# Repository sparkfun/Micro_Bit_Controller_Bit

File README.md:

SparkFun controller:bit - micro:bit Carrier Board (Qwiic)
========================================

<table class="table table-hover table-striped table-bordered">
  <tr align="center">
   <td></td>
   <td></td>
  </tr>
  <tr align="center">
   <td><i>SparkFun controller:bit - micro:bit Carrier Board (Qwiic)<br /> [ <a href="https://www.sparkfun.com/products/16129">DEV-16129</a> ]</i></td>
   <td><i>SparkFun micro:arcade kit for micro:bit v2.0 <br />[ <a href="https://www.sparkfun.com/products/16403">KIT-16403</a> ]</i></td>
  </tr>
</table>

The SparkFun controller:bit is a fun-filled “carrier” board for the micro:bit that, when combined with the micro:bit, provides you with a fully functional game system. Designed in a similar form factor to the classic Nintendo NES controller, the controller:bit is equipped with a four-direction “D-pad” on the left side of the board and two action buttons on the right side of the board. The two push buttons on the micro:bit in the center function as start and select. The back of the board also includes poke-home connectors if you decide to go retro by connecting connect arcade buttons and switches. Check out the micro:arcade kit if you decide to build your very own arcade cabinet using the micro:bit!

Repository Contents
-------------------

* **/Firmware** - Example code 
* **/Hardware** - Eagle design files (.brd, .sch)
* **/Hardware/Production** - Production panel files (.brd)

Documentation
--------------
* **[Library](https://github.com/sparkfun/pxt-gamer-bit)** - PXT controller:bit firmware
* **[Micro:Arcade Kit Experiment Guide](https://learn.sparkfun.com/tutorials/microarcade-kit-experiment-guide/)** -  Experiment guide using the controller:bit carrier board.
* **[Wireless Remote Control with micro:bit](https://learn.sparkfun.com/tutorials/wireless-remote-control-with-microbit)** - Project guide using the micro:bot and micro:arcade kits. By utilizing the radio blocks, you can wirelessly control the micro:bot using the controller:bit.

Version History
---------------

* [SparkFun controller:bit - micro:bit Carrier Board (Qwiic)](https://www.sparkfun.com/products/16129) - Latest and greatest (has qwiic connector)
* [SparkFun gamer:bit](https://www.sparkfun.com/products/14215) - Initial product (no qwiic connector)

Product Versions
----------------

* [KIT-16403](https://www.sparkfun.com/products/16403) - Kit with the controller:bit
* [DEV-16129](https://www.sparkfun.com/products/16129) - V21, revision and renamed as controller:bit
* [KIT-14218](https://www.sparkfun.com/products/14218) - Kit with the gamer:bit
* [DEV-14215](https://www.sparkfun.com/products/14215) - v10, Initial release as the gamer:bit

License Information
-------------------

This product is _**open source**_! 

Please review the LICENSE.md file for license information. 

If you have any questions or concerns on licensing, please contact technical support on our [SparkFun forums](https://forum.sparkfun.com/viewforum.php?f=152).

Distributed as-is; no warranty is given.

- Your friends at SparkFun.

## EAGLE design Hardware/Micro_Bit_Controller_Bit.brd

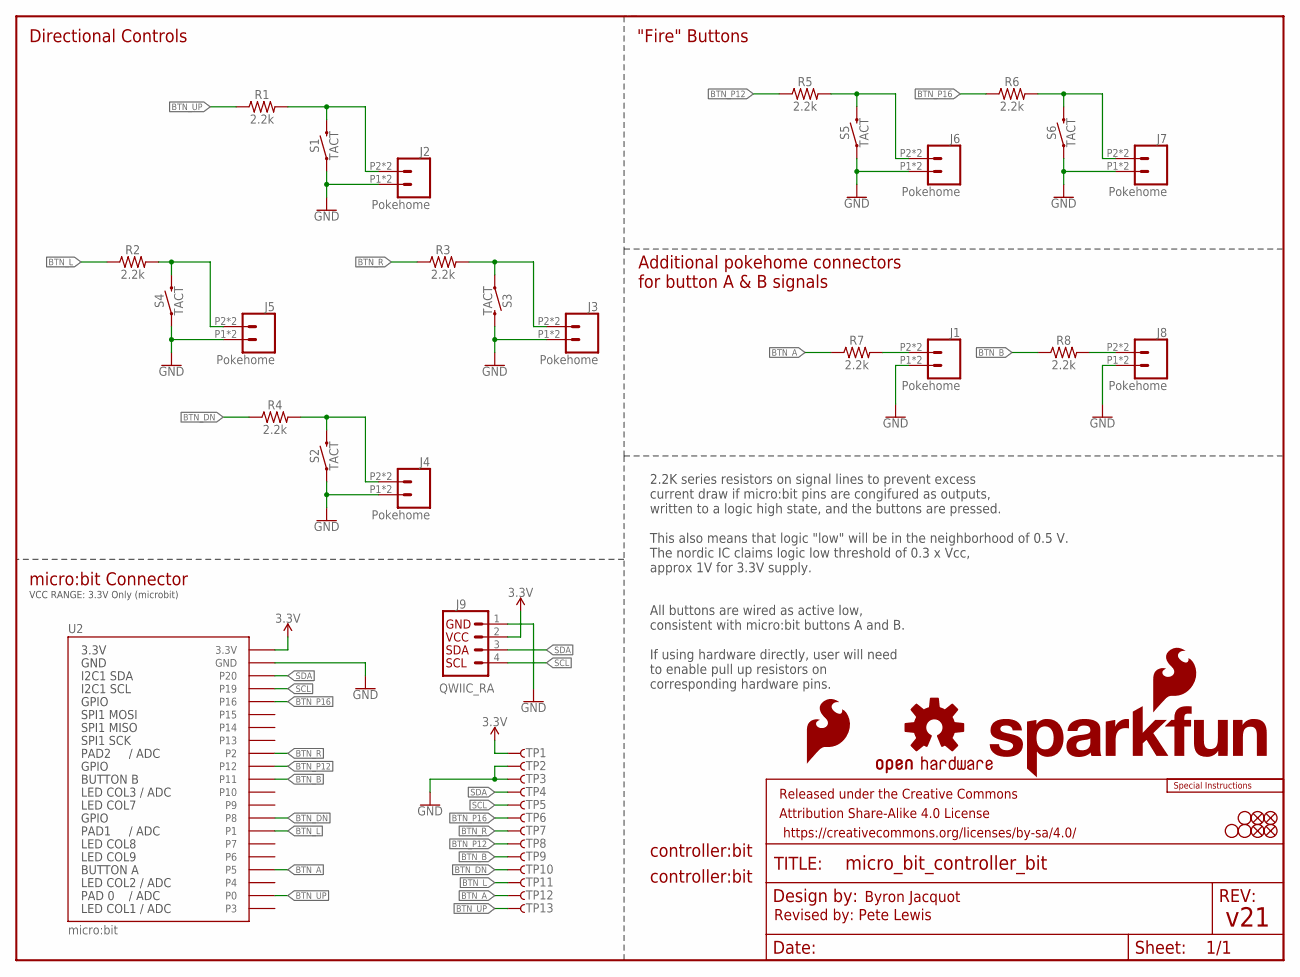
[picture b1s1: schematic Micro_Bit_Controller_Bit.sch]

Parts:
FD1, FD2, FD3, FD4: FIDUCIALUFIDUCIAL; FIDUCIAL-MICRO
FRAME1: FRAME-LETTER; CREATIVE_COMMONS
H1, H2, H3: STAND-OFF
J1, J2, J3, J4, J5, J6, J7, J8: Pokehome; 1X02_POKEHOME
J9: QWIIC_RA; JST04_1MM_RA
LOGO1: SFE_LOGO_FLAME.2_INCH; SFE_LOGO_FLAME_.2
LOGO2: OSHW-LOGOL; OSHW-LOGO-L
LOGO3: SFE_LOGO_NAME_FLAME.3_INCH; SFE_LOGO_NAME_FLAME_.3
R1, R2, R3, R4, R5, R6, R7, R8: 2.2k; 0603
S1, S2, S3, S4, S5, S6: TACT; TACTILE_SWITCH_SMD_12MM
TP1, TP2, TP3, TP4, TP5, TP6, TP7, TP8, TP9, TP10, TP11, TP12, TP13: TEST-POINT3X5; PAD.03X.05
U2: micro:bit; MICRO:BIT-RA_SMD
U$1: SPECIAL_INSTRUCTIONS-ORDERING; ORDERING_INSTRUCTIONS
U$3, U$6: LOGO-CONTROLLER_BIT

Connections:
3.3V: J9.2, TP1.P$1, U2.P$27 (3.3V), U2.P$28 (3.3V), U2.P$29 (3.3V), U2.P$30 (3.3V), U2.P$31 (3.3V), U2.P$32 (3.3V)
BTN_A: R7.1, TP12.P$1, U2.P$7 (P5)
BTN_B: R8.1, TP9.P$1, U2.P$17 (P11)
BTN_DN: R4.1, TP10.P$1, U2.P$14 (P8)
BTN_L: R2.1, TP11.P$1, U2.P$10 (P1), U2.P$11 (P1), U2.P$12 (P1), U2.P$13 (P1)
BTN_P12: R5.1, TP8.P$1, U2.P$18 (P12)
BTN_P16: R6.1, TP6.P$1, U2.P$26 (P16)
BTN_R: R3.1, TP7.P$1, U2.P$19 (P2), U2.P$20 (P2), U2.P$21 (P2), U2.P$22 (P2)
BTN_UP: R1.1, TP13.P$1, U2.P$2 (P0), U2.P$3 (P0), U2.P$4 (P0), U2.P$5 (P0)
GND: J1.P1 (1), J1.P3 (1), J2.P1 (1), J2.P3 (1), J3.P1 (1), J3.P3 (1), J4.P1 (1), J4.P3 (1), J5.P1 (1), J5.P3 (1), J6.P1 (1), J6.P3 (1), J7.P1 (1), J7.P3 (1), J8.P1 (1), J8.P3 (1), J9.1, S1.1, S2.1, S3.3 (2), S4.1, S5.1, S6.1, TP2.P$1, TP3.P$1, U2.P$35 (GND), U2.P$36 (GND), U2.P$37 (GND), U2.P$38 (GND), U2.P$39 (GND), U2.P$40 (GND)
unnamed: J2.P2 (2), J2.P4 (2), R1.2, S1.3 (2)
unnamed: J5.P2 (2), J5.P4 (2), R2.2, S4.3 (2)
unnamed: J4.P2 (2), J4.P4 (2), R4.2, S2.3 (2)
unnamed: J3.P2 (2), J3.P4 (2), R3.2, S3.1
unnamed: J7.P2 (2), J7.P4 (2), R6.2, S6.3 (2)
unnamed: J8.P2 (2), J8.P4 (2), R8.2
unnamed: J1.P2 (2), J1.P4 (2), R7.2
unnamed: J6.P2 (2), J6.P4 (2), R5.2, S5.3 (2)
SCL: J9.4, TP5.P$1, U2.P$33 (P19)
SDA: J9.3, TP4.P$1, U2.P$34 (P20)

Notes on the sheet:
Byron Jacquot
v21
All buttons are wired as active low, consistent with micro:bit buttons A and B. If using hardware directly, user will need to enable pull up resistors on corresponding hardware pins.
2.2K series resistors on signal lines to prevent excess current draw if micro:bit pins are congifured as outputs, written to a logic high state, and the buttons are pressed. This also means that logic "low" will be in the neighborhood of 0.5 V. The nordic IC claims logic low threshold of 0.3 x Vcc,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
Additional pokehome connectors for button A & B signals
Directional Controls
"Fire" Buttons
micro:bit Connector
Revised by: Pete Lewis
VCC RANGE: 3.3V Only (microbit)

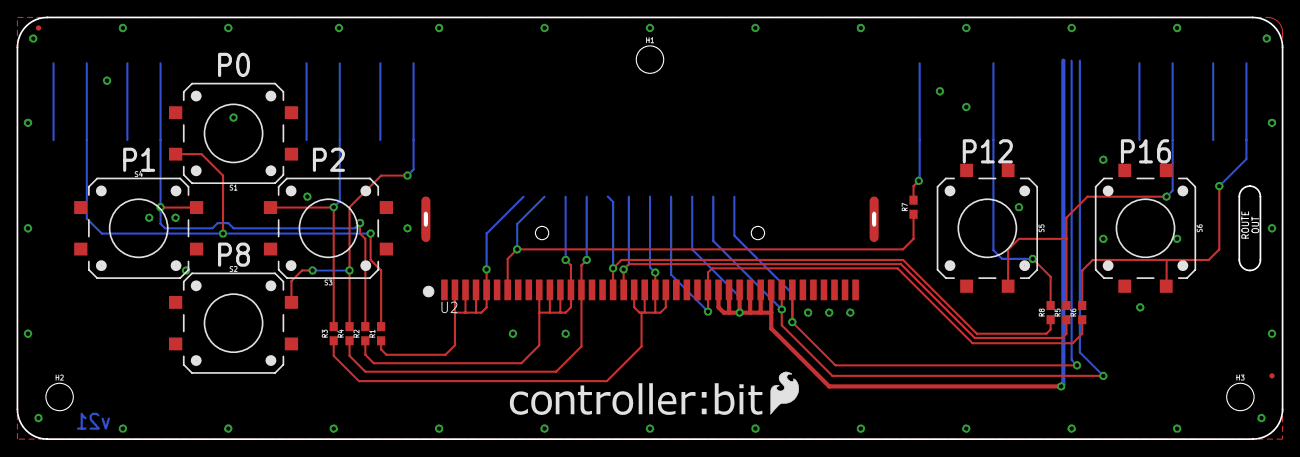
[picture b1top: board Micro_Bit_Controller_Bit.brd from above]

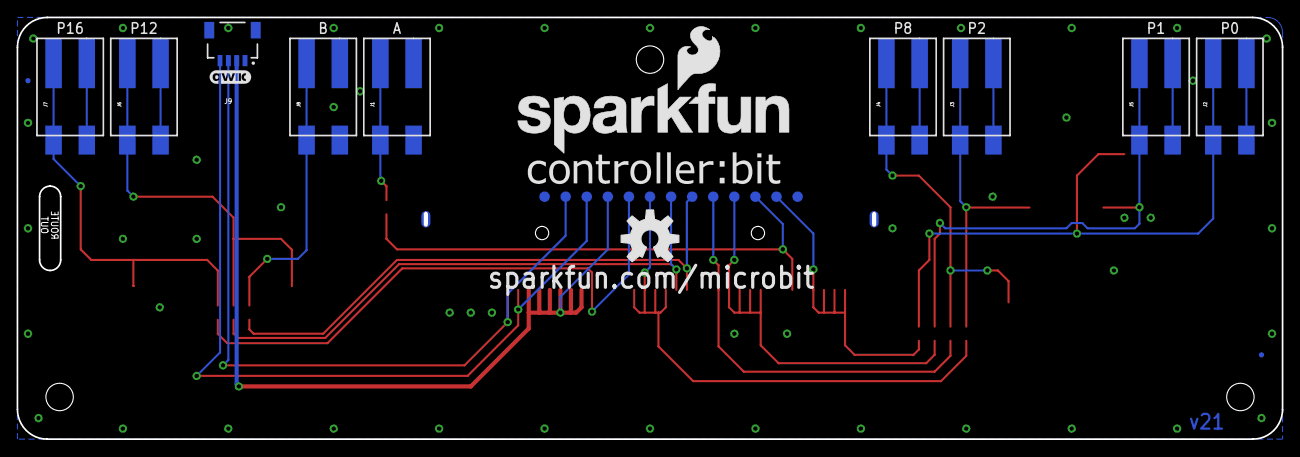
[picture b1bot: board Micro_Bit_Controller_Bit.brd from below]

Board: 2 copper layers, 152.1 x 50.5 mm, 52 parts (28 on the bottom side), 20 nets.

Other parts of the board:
U$2: QWIIC_5MM

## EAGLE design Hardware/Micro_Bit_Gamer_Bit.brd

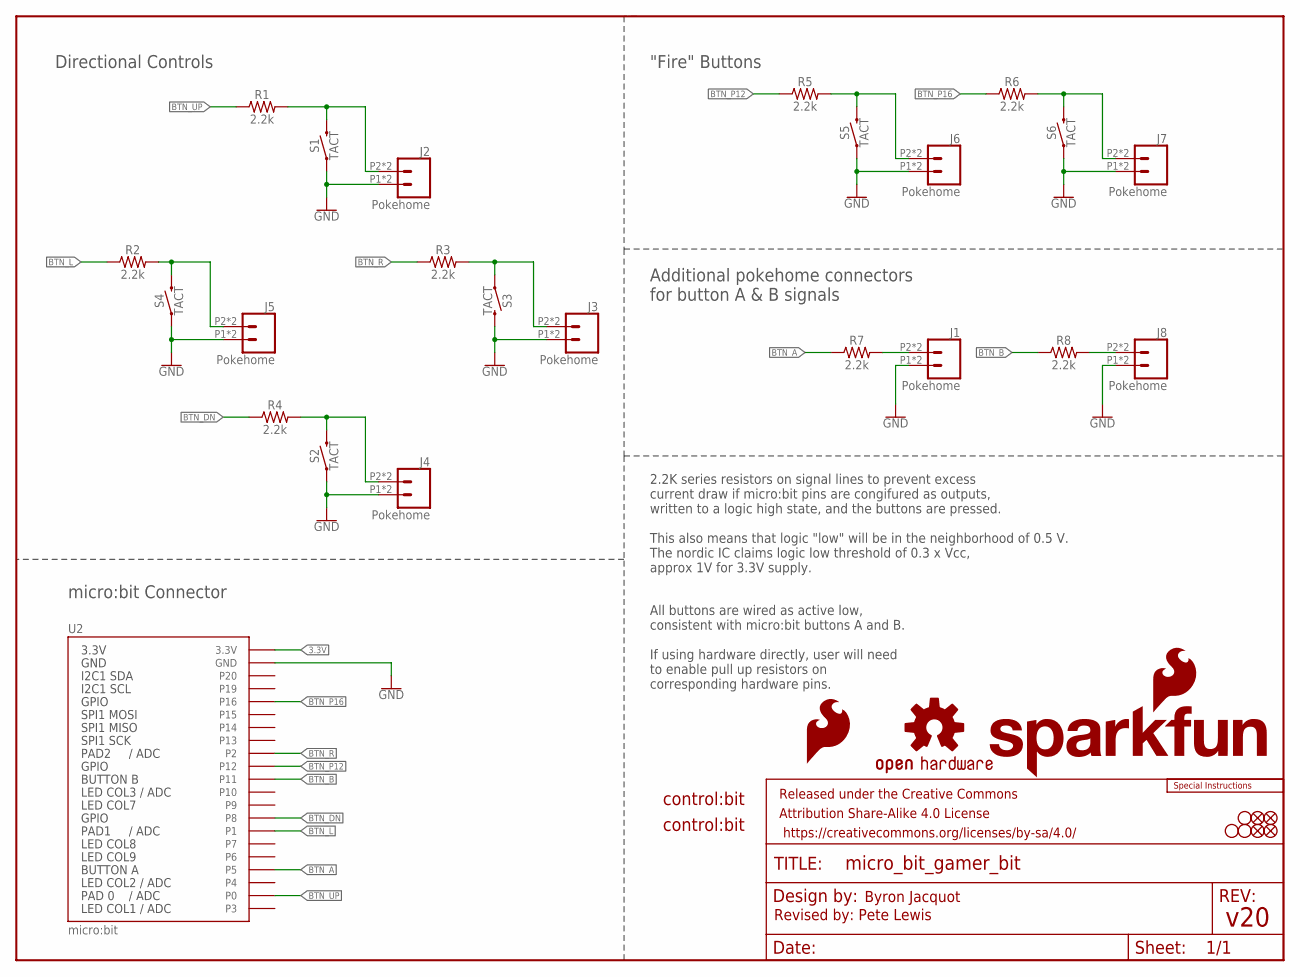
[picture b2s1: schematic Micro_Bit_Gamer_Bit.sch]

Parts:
FD1, FD2, FD3, FD4: FIDUCIALUFIDUCIAL; FIDUCIAL-MICRO
FRAME1: FRAME-LETTER; CREATIVE_COMMONS
H1, H2, H3: STAND-OFF
J1, J2, J3, J4, J5, J6, J7, J8: Pokehome; 1X02_POKEHOME
LOGO1: SFE_LOGO_FLAME.2_INCH; SFE_LOGO_FLAME_.2
LOGO2: OSHW-LOGOL; OSHW-LOGO-L
LOGO3: SFE_LOGO_NAME_FLAME.3_INCH; SFE_LOGO_NAME_FLAME_.3
R1, R2, R3, R4, R5, R6, R7, R8: 2.2k; 0603
S1, S2, S3, S4, S5, S6: TACT; TACTILE_SWITCH_SMD_12MM
U2: micro:bit; MICRO:BIT-RA_SMD
U$1: SPECIAL_INSTRUCTIONS-ORDERING; ORDERING_INSTRUCTIONS
U$4, U$5: LOGO-CONTROLBIT

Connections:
3.3V: U2.P$27 (3.3V), U2.P$28 (3.3V), U2.P$29 (3.3V), U2.P$30 (3.3V), U2.P$31 (3.3V), U2.P$32 (3.3V); also elsewhere on the board
BTN_A: R7.1, U2.P$7 (P5)
BTN_B: R8.1, U2.P$17 (P11)
BTN_DN: R4.1, U2.P$14 (P8)
BTN_L: R2.1, U2.P$10 (P1), U2.P$11 (P1), U2.P$12 (P1), U2.P$13 (P1)
BTN_P12: R5.1, U2.P$18 (P12)
BTN_P16: R6.1, U2.P$26 (P16)
BTN_R: R3.1, U2.P$19 (P2), U2.P$20 (P2), U2.P$21 (P2), U2.P$22 (P2)
BTN_UP: R1.1, U2.P$2 (P0), U2.P$3 (P0), U2.P$4 (P0), U2.P$5 (P0)
GND: J1.P1 (1), J1.P3 (1), J2.P1 (1), J2.P3 (1), J3.P1 (1), J3.P3 (1), J4.P1 (1), J4.P3 (1), J5.P1 (1), J5.P3 (1), J6.P1 (1), J6.P3 (1), J7.P1 (1), J7.P3 (1), J8.P1 (1), J8.P3 (1), S1.1, S2.1, S3.3 (2), S4.1, S5.1, S6.1, U2.P$35 (GND), U2.P$36 (GND), U2.P$37 (GND), U2.P$38 (GND), U2.P$39 (GND), U2.P$40 (GND); also elsewhere on the board
unnamed: J2.P2 (2), J2.P4 (2), R1.2, S1.3 (2)
unnamed: J5.P2 (2), J5.P4 (2), R2.2, S4.3 (2)
unnamed: J4.P2 (2), J4.P4 (2), R4.2, S2.3 (2)
unnamed: J3.P2 (2), J3.P4 (2), R3.2, S3.1
unnamed: J7.P2 (2), J7.P4 (2), R6.2, S6.3 (2)
unnamed: J8.P2 (2), J8.P4 (2), R8.2
unnamed: J1.P2 (2), J1.P4 (2), R7.2
unnamed: J6.P2 (2), J6.P4 (2), R5.2, S5.3 (2)
SCL: U2.P$33 (P19); also elsewhere on the board
SDA: U2.P$34 (P20); also elsewhere on the board

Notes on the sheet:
Byron Jacquot
v20
All buttons are wired as active low, consistent with micro:bit buttons A and B. If using hardware directly, user will need to enable pull up resistors on corresponding hardware pins.
2.2K series resistors on signal lines to prevent excess current draw if micro:bit pins are congifured as outputs, written to a logic high state, and the buttons are pressed. This also means that logic "low" will be in the neighborhood of 0.5 V. The nordic IC claims logic low threshold of 0.3 x Vcc,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
Additional pokehome connectors for button A & B signals
Directional Controls
"Fire" Buttons
micro:bit Connector
Revised by: Pete Lewis

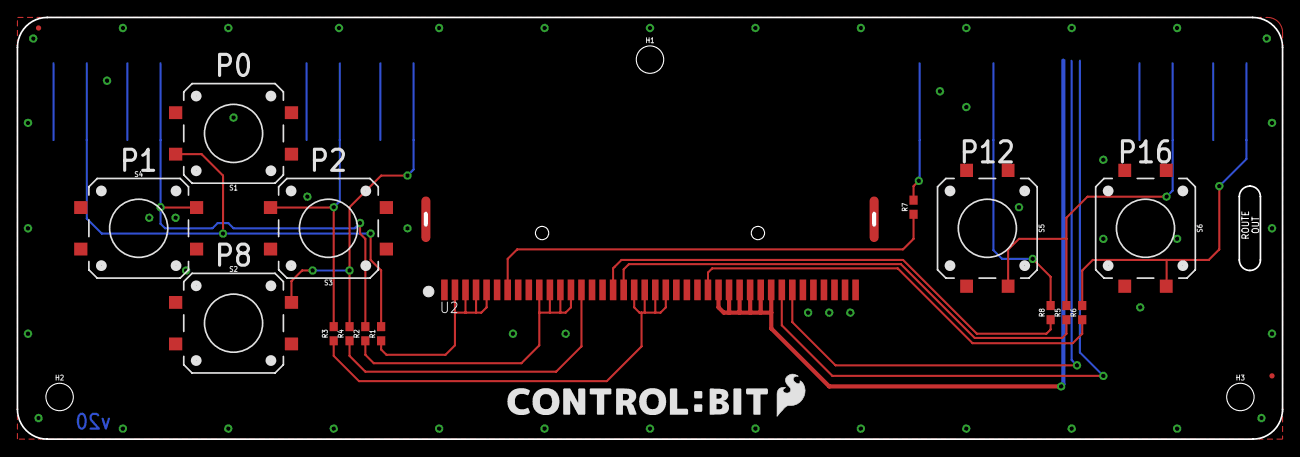
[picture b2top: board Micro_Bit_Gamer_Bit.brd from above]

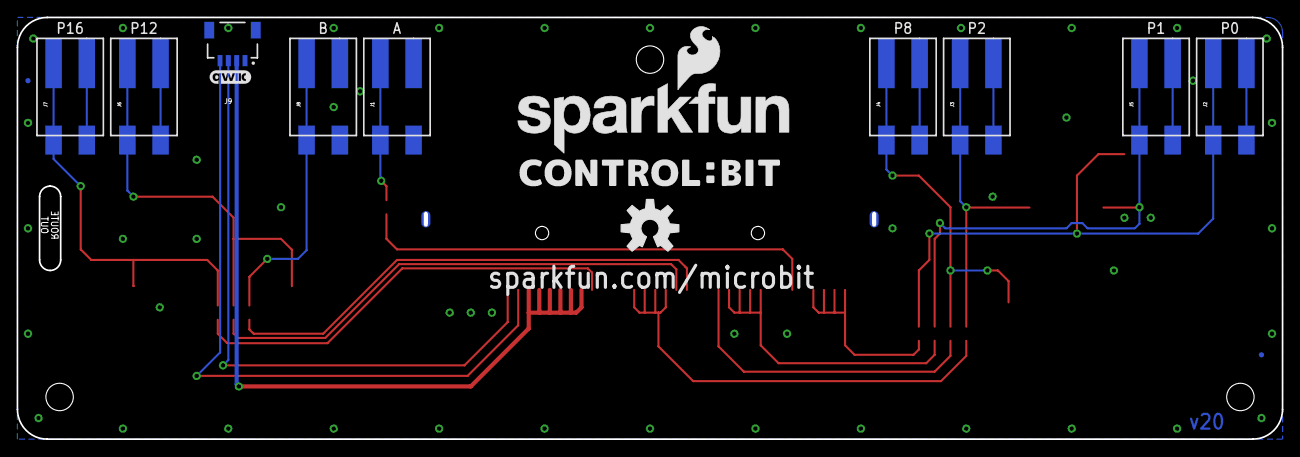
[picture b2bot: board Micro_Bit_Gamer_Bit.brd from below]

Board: 2 copper layers, 152.1 x 50.5 mm, 39 parts (15 on the bottom side), 20 nets.

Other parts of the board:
J9: QWIIC_RA; JST04_1MM_RA
U$2: QWIIC_5MM

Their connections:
3.3V: J9.2; also elsewhere on the board
GND: J9.1; also elsewhere on the board
SCL: J9.4; also elsewhere on the board
SDA: J9.3; also elsewhere on the board

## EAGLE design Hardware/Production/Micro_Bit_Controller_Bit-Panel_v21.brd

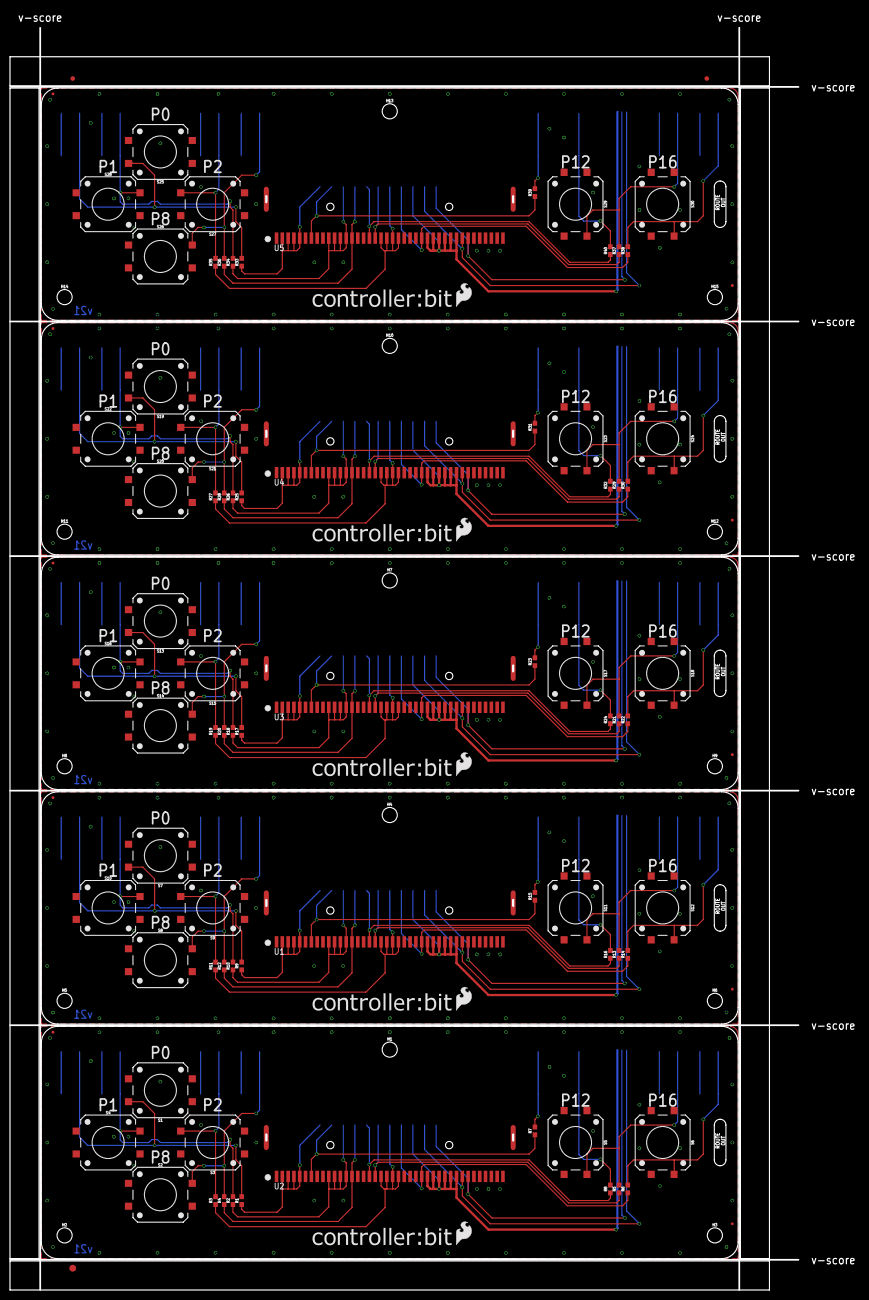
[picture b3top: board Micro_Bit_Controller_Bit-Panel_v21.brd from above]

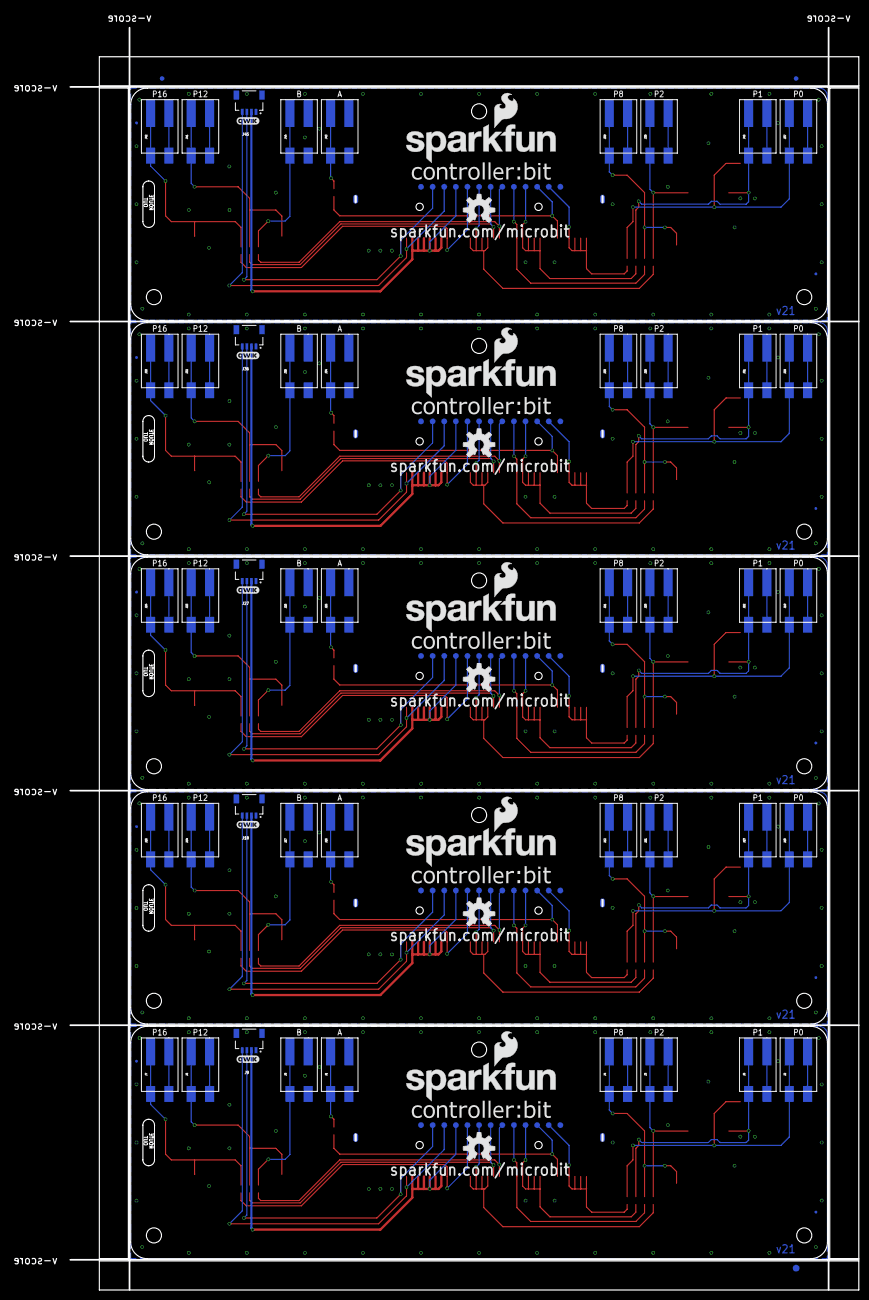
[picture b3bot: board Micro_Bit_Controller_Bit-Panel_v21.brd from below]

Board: 2 copper layers, 185.5 x 279.8 mm, 256 parts (143 on the bottom side), 100 nets.

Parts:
E$1, E$2, E$3, E$4: FIDUCIAL-1X2
E$5, E$6: FIDUCIAL-1.5X3
FD1, FD2, FD3, FD4, FD5, FD6, FD7, FD8, FD9, FD10, FD11, FD12, FD13, FD14, FD15, FD16, FD17, FD18, FD19, FD20: FIDUCIALUFIDUCIAL; FIDUCIAL-MICRO
H1, H2, H3, H4, H5, H6, H7, H8, H9, H10, H11, H12, H13, H14, H15: STAND-OFF
J1, J2, J3, J4, J5, J6, J7, J8, J10, J11, J12, J13, J14, J15, J16, J17, J19, J20, J21, J22, J23, J24, J25, J26, J28, J29, J30, J31, J32, J33, J34, J35, J37, J38, J39, J40, J41, J42, J43, J44: Pokehome; 1X02_POKEHOME
J9, J18, J27, J36, J45: QWIIC_RA; JST04_1MM_RA
LOGO1, LOGO4, LOGO7, LOGO10, LOGO13: SFE_LOGO_FLAME.2_INCH; SFE_LOGO_FLAME_.2
LOGO2, LOGO5, LOGO8, LOGO11, LOGO14: OSHW-LOGOL; OSHW-LOGO-L
LOGO3, LOGO6, LOGO9, LOGO12, LOGO15: SFE_LOGO_NAME_FLAME.3_INCH; SFE_LOGO_NAME_FLAME_.3
R1, R2, R3, R4, R5, R6, R7, R8, R9, R10, R11, R12, R13, R14, R15, R16, R17, R18, R19, R20, R21, R22, R23, R24, R25, R26, R27, R28, R29, R30, R31, R32, R33, R34, R35, R36, R37, R38, R39, R40: 2.2k; 0603
S1, S2, S3, S4, S5, S6, S7, S8, S9, S10, S11, S12, S13, S14, S15, S16, S17, S18, S19, S20, S21, S22, S23, S24, S25, S26, S27, S28, S29, S30: TACT; TACTILE_SWITCH_SMD_12MM
TP1, TP2, TP3, TP4, TP5, TP6, TP7, TP8, TP9, TP10, TP11, TP12, TP13, TP14, TP15, TP16, TP17, TP18, TP19, TP20, TP21, TP22, TP23, TP24, TP25, TP26, TP27, TP28, TP29, TP30, TP31, TP32, TP33, TP34, TP35, TP36, TP37, TP38, TP39, TP40, TP41, TP42, TP43, TP44, TP45, TP46, TP47, TP48, TP49, TP50, TP51, TP52, TP53, TP54, TP55, TP56, TP57, TP58, TP59, TP60, TP61, TP62, TP63, TP64, TP65: TEST-POINT3X5; PAD.03X.05
U1, U2, U3, U4, U5: micro:bit; MICRO:BIT-RA_SMD
U$1, U$2, U$7, U$10, U$13: QWIIC_5MM
U$3, U$4, U$5, U$6, U$8, U$9, U$11, U$12, U$14, U$15: LOGO-CONTROLLER_BIT

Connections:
3.3V: J9.2, TP1.P$1, U2.P$27, U2.P$28, U2.P$29, U2.P$30, U2.P$31, U2.P$32
3.3V1: J18.2, TP14.P$1, U1.P$27, U1.P$28, U1.P$29, U1.P$30, U1.P$31, U1.P$32
3.3V2: J27.2, TP27.P$1, U3.P$27, U3.P$28, U3.P$29, U3.P$30, U3.P$31, U3.P$32
3.3V3: J36.2, TP40.P$1, U4.P$27, U4.P$28, U4.P$29, U4.P$30, U4.P$31, U4.P$32
3.3V4: J45.2, TP53.P$1, U5.P$27, U5.P$28, U5.P$29, U5.P$30, U5.P$31, U5.P$32
BTN_A: R7.1, TP12.P$1, U2.P$7
BTN_A1: R15.1, TP25.P$1, U1.P$7
BTN_A2: R23.1, TP38.P$1, U3.P$7
BTN_A3: R31.1, TP51.P$1, U4.P$7
BTN_A4: R39.1, TP64.P$1, U5.P$7
BTN_B: R8.1, TP9.P$1, U2.P$17
BTN_B1: R16.1, TP22.P$1, U1.P$17
BTN_B2: R24.1, TP35.P$1, U3.P$17
BTN_B3: R32.1, TP48.P$1, U4.P$17
BTN_B4: R40.1, TP61.P$1, U5.P$17
BTN_DN: R4.1, TP10.P$1, U2.P$14
BTN_DN1: R12.1, TP23.P$1, U1.P$14
BTN_DN2: R20.1, TP36.P$1, U3.P$14
BTN_DN3: R28.1, TP49.P$1, U4.P$14
BTN_DN4: R36.1, TP62.P$1, U5.P$14
BTN_L: R2.1, TP11.P$1, U2.P$10, U2.P$11, U2.P$12, U2.P$13
BTN_L1: R10.1, TP24.P$1, U1.P$10, U1.P$11, U1.P$12, U1.P$13
BTN_L2: R18.1, TP37.P$1, U3.P$10, U3.P$11, U3.P$12, U3.P$13
BTN_L3: R26.1, TP50.P$1, U4.P$10, U4.P$11, U4.P$12, U4.P$13
BTN_L4: R34.1, TP63.P$1, U5.P$10, U5.P$11, U5.P$12, U5.P$13
BTN_P1: R14.1, TP19.P$1, U1.P$26
BTN_P2: R13.1, TP21.P$1, U1.P$18
BTN_P3: R22.1, TP32.P$1, U3.P$26
BTN_P4: R21.1, TP34.P$1, U3.P$18
BTN_P5: R30.1, TP45.P$1, U4.P$26
BTN_P6: R29.1, TP47.P$1, U4.P$18
BTN_P7: R38.1, TP58.P$1, U5.P$26
BTN_P8: R37.1, TP60.P$1, U5.P$18
BTN_P12: R5.1, TP8.P$1, U2.P$18
BTN_P16: R6.1, TP6.P$1, U2.P$26
BTN_R: R3.1, TP7.P$1, U2.P$19, U2.P$20, U2.P$21, U2.P$22
BTN_R1: R11.1, TP20.P$1, U1.P$19, U1.P$20, U1.P$21, U1.P$22
BTN_R2: R19.1, TP33.P$1, U3.P$19, U3.P$20, U3.P$21, U3.P$22
BTN_R3: R27.1, TP46.P$1, U4.P$19, U4.P$20, U4.P$21, U4.P$22
BTN_R4: R35.1, TP59.P$1, U5.P$19, U5.P$20, U5.P$21, U5.P$22
BTN_UP: R1.1, TP13.P$1, U2.P$2, U2.P$3, U2.P$4, U2.P$5
BTN_UP1: R9.1, TP26.P$1, U1.P$2, U1.P$3, U1.P$4, U1.P$5
BTN_UP2: R17.1, TP39.P$1, U3.P$2, U3.P$3, U3.P$4, U3.P$5
BTN_UP3: R25.1, TP52.P$1, U4.P$2, U4.P$3, U4.P$4, U4.P$5
BTN_UP4: R33.1, TP65.P$1, U5.P$2, U5.P$3, U5.P$4, U5.P$5
GND: J1.P1, J1.P3, J2.P1, J2.P3, J3.P1, J3.P3, J4.P1, J4.P3, J5.P1, J5.P3, J6.P1, J6.P3, J7.P1, J7.P3, J8.P1, J8.P3, J9.1, S1.1, S2.1, S3.3, S4.1, S5.1, S6.1, TP2.P$1, TP3.P$1, U2.P$35, U2.P$36, U2.P$37, U2.P$38, U2.P$39, U2.P$40
GND1: J10.P1, J10.P3, J11.P1, J11.P3, J12.P1, J12.P3, J13.P1, J13.P3, J14.P1, J14.P3, J15.P1, J15.P3, J16.P1, J16.P3, J17.P1, J17.P3, J18.1, S7.1, S8.1, S9.3, S10.1, S11.1, S12.1, TP15.P$1, TP16.P$1, U1.P$35, U1.P$36, U1.P$37, U1.P$38, U1.P$39, U1.P$40
GND2: J19.P1, J19.P3, J20.P1, J20.P3, J21.P1, J21.P3, J22.P1, J22.P3, J23.P1, J23.P3, J24.P1, J24.P3, J25.P1, J25.P3, J26.P1, J26.P3, J27.1, S13.1, S14.1, S15.3, S16.1, S17.1, S18.1, TP28.P$1, TP29.P$1, U3.P$35, U3.P$36, U3.P$37, U3.P$38, U3.P$39, U3.P$40
GND3: J28.P1, J28.P3, J29.P1, J29.P3, J30.P1, J30.P3, J31.P1, J31.P3, J32.P1, J32.P3, J33.P1, J33.P3, J34.P1, J34.P3, J35.P1, J35.P3, J36.1, S19.1, S20.1, S21.3, S22.1, S23.1, S24.1, TP41.P$1, TP42.P$1, U4.P$35, U4.P$36, U4.P$37, U4.P$38, U4.P$39, U4.P$40
GND4: J37.P1, J37.P3, J38.P1, J38.P3, J39.P1, J39.P3, J40.P1, J40.P3, J41.P1, J41.P3, J42.P1, J42.P3, J43.P1, J43.P3, J44.P1, J44.P3, J45.1, S25.1, S26.1, S27.3, S28.1, S29.1, S30.1, TP54.P$1, TP55.P$1, U5.P$35, U5.P$36, U5.P$37, U5.P$38, U5.P$39, U5.P$40
unnamed: J2.P2, J2.P4, R1.2, S1.3
unnamed: J5.P2, J5.P4, R2.2, S4.3
unnamed: J4.P2, J4.P4, R4.2, S2.3
unnamed: J3.P2, J3.P4, R3.2, S3.1
unnamed: J7.P2, J7.P4, R6.2, S6.3
unnamed: J8.P2, J8.P4, R8.2
unnamed: J1.P2, J1.P4, R7.2
unnamed: J10.P2, J10.P4, R9.2, S7.3
unnamed: J13.P2, J13.P4, R10.2, S10.3
unnamed: J12.P2, J12.P4, R12.2, S8.3
unnamed: J11.P2, J11.P4, R11.2, S9.1
unnamed: J14.P2, J14.P4, R13.2, S11.3
unnamed: J15.P2, J15.P4, R14.2, S12.3
unnamed: J16.P2, J16.P4, R15.2
unnamed: J17.P2, J17.P4, R16.2
unnamed: J19.P2, J19.P4, R17.2, S13.3
unnamed: J22.P2, J22.P4, R18.2, S16.3
unnamed: J21.P2, J21.P4, R20.2, S14.3
unnamed: J20.P2, J20.P4, R19.2, S15.1
unnamed: J23.P2, J23.P4, R21.2, S17.3
unnamed: J24.P2, J24.P4, R22.2, S18.3
unnamed: J25.P2, J25.P4, R23.2
unnamed: J26.P2, J26.P4, R24.2
unnamed: J28.P2, J28.P4, R25.2, S19.3
unnamed: J31.P2, J31.P4, R26.2, S22.3
unnamed: J30.P2, J30.P4, R28.2, S20.3
unnamed: J29.P2, J29.P4, R27.2, S21.1
unnamed: J32.P2, J32.P4, R29.2, S23.3
unnamed: J33.P2, J33.P4, R30.2, S24.3
unnamed: J34.P2, J34.P4, R31.2
unnamed: J35.P2, J35.P4, R32.2
unnamed: J37.P2, J37.P4, R33.2, S25.3
unnamed: J40.P2, J40.P4, R34.2, S28.3
unnamed: J39.P2, J39.P4, R36.2, S26.3
unnamed: J38.P2, J38.P4, R35.2, S27.1
unnamed: J41.P2, J41.P4, R37.2, S29.3
unnamed: J42.P2, J42.P4, R38.2, S30.3
unnamed: J43.P2, J43.P4, R39.2
unnamed: J44.P2, J44.P4, R40.2
unnamed: J6.P2, J6.P4, R5.2, S5.3
SCL: J9.4, TP5.P$1, U2.P$33
SCL1: J18.4, TP18.P$1, U1.P$33
SCL2: J27.4, TP31.P$1, U3.P$33
SCL3: J36.4, TP44.P$1, U4.P$33
SCL4: J45.4, TP57.P$1, U5.P$33
SDA: J9.3, TP4.P$1, U2.P$34
SDA1: J18.3, TP17.P$1, U1.P$34
SDA2: J27.3, TP30.P$1, U3.P$34
SDA3: J36.3, TP43.P$1, U4.P$34
SDA4: J45.3, TP56.P$1, U5.P$34

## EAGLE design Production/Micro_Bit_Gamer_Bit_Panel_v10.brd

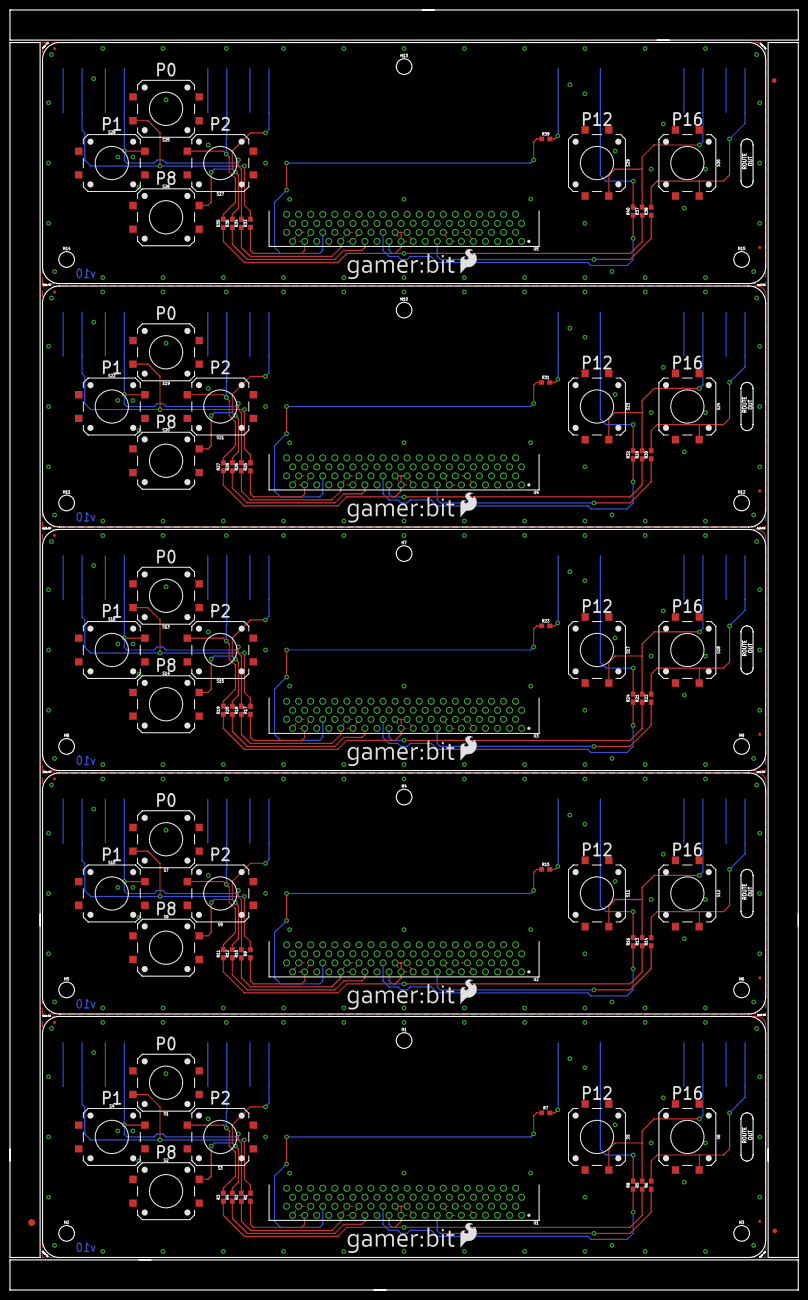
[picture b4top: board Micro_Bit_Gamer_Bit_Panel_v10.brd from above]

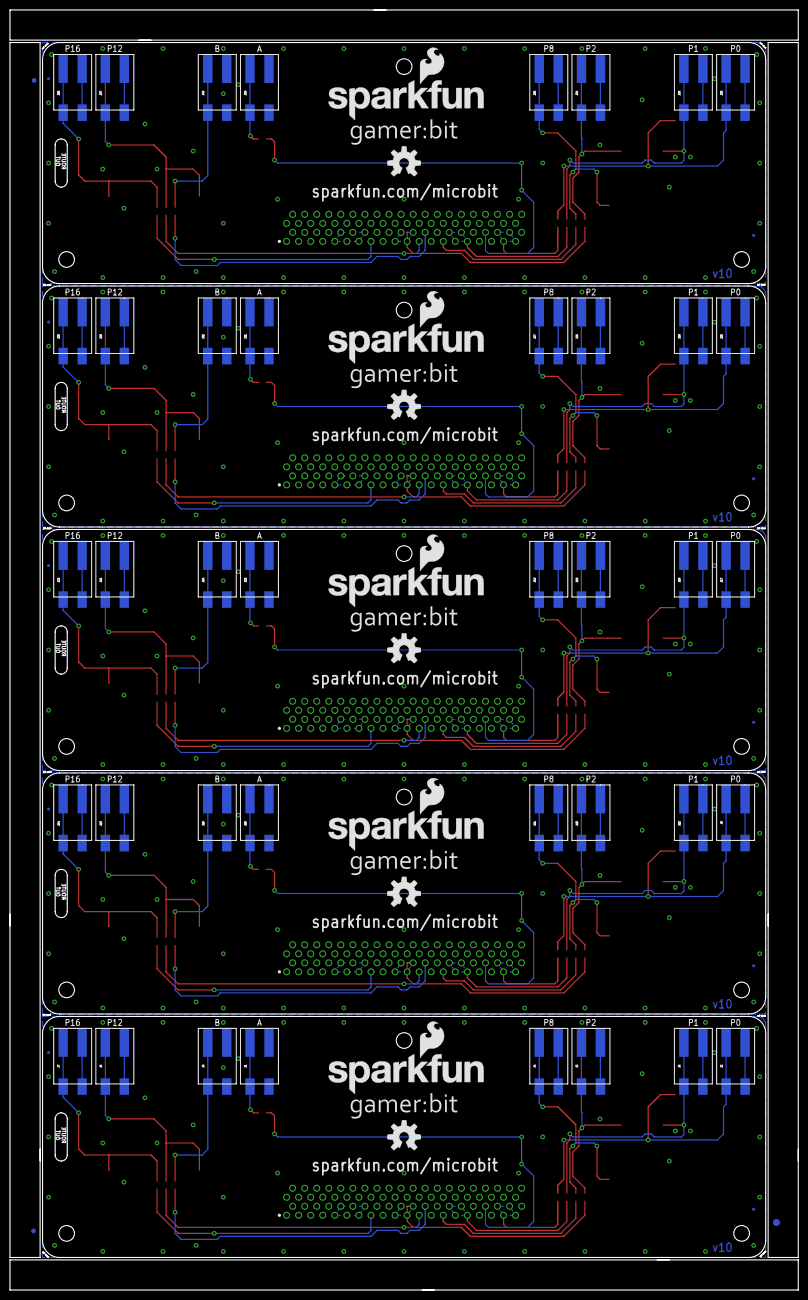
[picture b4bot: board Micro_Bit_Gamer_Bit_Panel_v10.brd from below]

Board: 2 copper layers, 166.1 x 269.7 mm, 181 parts (68 on the bottom side), 90 nets.

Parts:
E$1, E$2: FIDUCIAL-1.5X3
E$3, E$4, E$5, E$7: FIDUCIAL-1X2
FD1, FD2, FD3, FD4, FD5, FD6, FD7, FD8, FD9, FD10, FD11, FD12, FD13, FD14, FD15, FD16, FD17, FD18, FD19, FD20: FIDUCIALUFIDUCIAL; FIDUCIAL-MICRO
H1, H2, H3, H4, H5, H6, H7, H8, H9, H10, H11, H12, H13, H14, H15: STAND-OFF
J1, J2, J3, J4, J5, J6, J7, J8, J9, J10, J11, J12, J13, J14, J15, J16, J17, J18, J19, J20, J21, J22, J23, J24, J25, J26, J27, J28, J29, J30, J31, J32, J33, J34, J35, J36, J37, J38, J39, J40: Pokehome; 1X02_POKEHOME
LOGO1, LOGO4, LOGO7, LOGO10, LOGO13: SFE_LOGO_FLAME.2_INCH; SFE_LOGO_FLAME_.2
LOGO2, LOGO5, LOGO8, LOGO11, LOGO14: OSHW-LOGOL; OSHW-LOGO-L
LOGO3, LOGO6, LOGO9, LOGO12, LOGO15: SFE_LOGO_NAME_FLAME.3_INCH; SFE_LOGO_NAME_FLAME_.3
R1, R2, R3, R4, R5, R6, R7, R8, R9, R10, R11, R12, R13, R14, R15, R16, R17, R18, R19, R20, R21, R22, R23, R24, R25, R26, R27, R28, R29, R30, R31, R32, R33, R34, R35, R36, R37, R38, R39, R40: 2.2k; 0603
S1, S2, S3, S4, S5, S6, S7, S8, S9, S10, S11, S12, S13, S14, S15, S16, S17, S18, S19, S20, S21, S22, S23, S24, S25, S26, S27, S28, S29, S30: TACT; TACTILE_SWITCH_SMD_12MM
U1, U2, U3, U4, U5: micro:bit; MICRO:BIT_RA_PTH
U$1, U$2, U$3, U$4, U$5, U$6, U$7, U$8, U$9, U$10: LOGO-GAMERBIT

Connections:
3.3V: U1.A9, U1.A10, U1.A11, U1.A12, U1.A13, U1.A14
3.3V1: U2.A9, U2.A10, U2.A11, U2.A12, U2.A13, U2.A14
3.3V2: U3.A9, U3.A10, U3.A11, U3.A12, U3.A13, U3.A14
3.3V3: U4.A9, U4.A10, U4.A11, U4.A12, U4.A13, U4.A14
3.3V4: U5.A9, U5.A10, U5.A11, U5.A12, U5.A13, U5.A14
BTN_A: R7.1, U1.A34
BTN_A1: R15.1, U2.A34
BTN_A2: R23.1, U3.A34
BTN_A3: R31.1, U4.A34
BTN_A4: R39.1, U5.A34
BTN_B: R8.1, U1.A24
BTN_B1: R16.1, U2.A24
BTN_B2: R24.1, U3.A24
BTN_B3: R32.1, U4.A24
BTN_B4: R40.1, U5.A24
BTN_DN: R4.1, U1.A27
BTN_DN1: R12.1, U2.A27
BTN_DN2: R20.1, U3.A27
BTN_DN3: R28.1, U4.A27
BTN_DN4: R36.1, U5.A27
BTN_L: R2.1, U1.A28, U1.A29, U1.A30, U1.A31
BTN_L1: R10.1, U2.A28, U2.A29, U2.A30, U2.A31
BTN_L2: R18.1, U3.A28, U3.A29, U3.A30, U3.A31
BTN_L3: R26.1, U4.A28, U4.A29, U4.A30, U4.A31
BTN_L4: R34.1, U5.A28, U5.A29, U5.A30, U5.A31
BTN_P1: R14.1, U2.A15
BTN_P2: R13.1, U2.A23
BTN_P3: R22.1, U3.A15
BTN_P4: R21.1, U3.A23
BTN_P5: R30.1, U4.A15
BTN_P6: R29.1, U4.A23
BTN_P7: R38.1, U5.A15
BTN_P8: R37.1, U5.A23
BTN_P12: R5.1, U1.A23
BTN_P16: R6.1, U1.A15
BTN_R: R3.1, U1.A19, U1.A20, U1.A21, U1.A22
BTN_R1: R11.1, U2.A19, U2.A20, U2.A21, U2.A22
BTN_R2: R19.1, U3.A19, U3.A20, U3.A21, U3.A22
BTN_R3: R27.1, U4.A19, U4.A20, U4.A21, U4.A22
BTN_R4: R35.1, U5.A19, U5.A20, U5.A21, U5.A22
BTN_UP: R1.1, U1.A36, U1.A37, U1.A38, U1.A39
BTN_UP1: R9.1, U2.A36, U2.A37, U2.A38, U2.A39
BTN_UP2: R17.1, U3.A36, U3.A37, U3.A38, U3.A39
BTN_UP3: R25.1, U4.A36, U4.A37, U4.A38, U4.A39
BTN_UP4: R33.1, U5.A36, U5.A37, U5.A38, U5.A39
GND: J1.P1, J1.P3, J2.P1, J2.P3, J3.P1, J3.P3, J4.P1, J4.P3, J5.P1, J5.P3, J6.P1, J6.P3, J7.P1, J7.P3, J8.P1, J8.P3, S1.1, S2.1, S3.3, S4.1, S5.1, S6.1, U1.A1, U1.A2, U1.A3, U1.A4, U1.A5, U1.A6
GND1: J9.P1, J9.P3, J10.P1, J10.P3, J11.P1, J11.P3, J12.P1, J12.P3, J13.P1, J13.P3, J14.P1, J14.P3, J15.P1, J15.P3, J16.P1, J16.P3, S7.1, S8.1, S9.3, S10.1, S11.1, S12.1, U2.A1, U2.A2, U2.A3, U2.A4, U2.A5, U2.A6
GND2: J17.P1, J17.P3, J18.P1, J18.P3, J19.P1, J19.P3, J20.P1, J20.P3, J21.P1, J21.P3, J22.P1, J22.P3, J23.P1, J23.P3, J24.P1, J24.P3, S13.1, S14.1, S15.3, S16.1, S17.1, S18.1, U3.A1, U3.A2, U3.A3, U3.A4, U3.A5, U3.A6
GND3: J25.P1, J25.P3, J26.P1, J26.P3, J27.P1, J27.P3, J28.P1, J28.P3, J29.P1, J29.P3, J30.P1, J30.P3, J31.P1, J31.P3, J32.P1, J32.P3, S19.1, S20.1, S21.3, S22.1, S23.1, S24.1, U4.A1, U4.A2, U4.A3, U4.A4, U4.A5, U4.A6
GND4: J33.P1, J33.P3, J34.P1, J34.P3, J35.P1, J35.P3, J36.P1, J36.P3, J37.P1, J37.P3, J38.P1, J38.P3, J39.P1, J39.P3, J40.P1, J40.P3, S25.1, S26.1, S27.3, S28.1, S29.1, S30.1, U5.A1, U5.A2, U5.A3, U5.A4, U5.A5, U5.A6
unnamed: J2.P2, J2.P4, R1.2, S1.3
unnamed: J5.P2, J5.P4, R2.2, S4.3
unnamed: J4.P2, J4.P4, R4.2, S2.3
unnamed: J3.P2, J3.P4, R3.2, S3.1
unnamed: J7.P2, J7.P4, R6.2, S6.3
unnamed: J8.P2, J8.P4, R8.2
unnamed: J1.P2, J1.P4, R7.2
unnamed: J9.P2, J9.P4, R9.2, S7.3
unnamed: J12.P2, J12.P4, R10.2, S10.3
unnamed: J11.P2, J11.P4, R12.2, S8.3
unnamed: J10.P2, J10.P4, R11.2, S9.1
unnamed: J13.P2, J13.P4, R13.2, S11.3
unnamed: J14.P2, J14.P4, R14.2, S12.3
unnamed: J15.P2, J15.P4, R15.2
unnamed: J16.P2, J16.P4, R16.2
unnamed: J17.P2, J17.P4, R17.2, S13.3
unnamed: J20.P2, J20.P4, R18.2, S16.3
unnamed: J19.P2, J19.P4, R20.2, S14.3
unnamed: J18.P2, J18.P4, R19.2, S15.1
unnamed: J21.P2, J21.P4, R21.2, S17.3
unnamed: J22.P2, J22.P4, R22.2, S18.3
unnamed: J23.P2, J23.P4, R23.2
unnamed: J24.P2, J24.P4, R24.2
unnamed: J25.P2, J25.P4, R25.2, S19.3
unnamed: J28.P2, J28.P4, R26.2, S22.3
unnamed: J27.P2, J27.P4, R28.2, S20.3
unnamed: J26.P2, J26.P4, R27.2, S21.1
unnamed: J29.P2, J29.P4, R29.2, S23.3
unnamed: J30.P2, J30.P4, R30.2, S24.3
unnamed: J31.P2, J31.P4, R31.2
unnamed: J32.P2, J32.P4, R32.2
unnamed: J33.P2, J33.P4, R33.2, S25.3
unnamed: J36.P2, J36.P4, R34.2, S28.3
unnamed: J35.P2, J35.P4, R36.2, S26.3
unnamed: J34.P2, J34.P4, R35.2, S27.1
unnamed: J37.P2, J37.P4, R37.2, S29.3
unnamed: J38.P2, J38.P4, R38.2, S30.3
unnamed: J39.P2, J39.P4, R39.2
unnamed: J40.P2, J40.P4, R40.2
unnamed: J6.P2, J6.P4, R5.2, S5.3

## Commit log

2017-03-14 Initial boilerplate checkin.
    Also added a library with the 80 pin edge connector in it.
2017-03-15 Library updates & draft of board.
2017-03-16 Adding pokehome connectors & a little test code
2017-03-28 Board routed, ready for review.
2017-03-28 Checking in test code for pins with onboard pullups.
    This worked with a fresh build of micropython, which includes the
    pinx.set_pull() function on pins.
    Pin12 also requires a read before it's usable as an input.
2017-03-30 Updates after review.
    See review minutes attached to bug for details.
2017-04-03 Engineering checklist touchups.
2017-04-05 Adjusting silk on directional buttons, as per checklist.
2017-04-11 Incorporating Edu Feedback.
    Pokehomes on back of board.
    Touched up logos & markings.
2017-04-18 Changed name font to match other microbit boards
2017-05-16 Moved right two buttons together by 0.3 inches
2017-05-24 Created version 1.0
2017-05-25 created panel v10
2017-07-21 updating repo with product release info
2017-07-21 fixing image urls
2019-01-08 micro:arcade Example Code HEX files
    Add compiled MakeCode example code used in kit.
2019-01-21 Add Wireless Remote Control with micro:bit examples
2019-12-09 Moved to SMD connector
2019-12-09 Update silk to control bit
    On both front and back.
2019-12-09 Cleaned up a coulpe traces added vias for pour
2019-12-10 Added qwiic connector to back side
2019-12-10 renaming eagle files to match new product name
2019-12-11 Updated contro bit text silk to match other boards
2019-12-11 Adding test points
2019-12-11 vector fonts in sch
2019-12-11 library thing - control bit text device now in SFE aethetics
2019-12-11 sch cleanup and vcc range
2019-12-11 bumped test ppoints to larger size
    also rearragned VCC pin over so it wasn't right next to GND, to help avoid accidental jumpers between VCC and GND.
2019-12-11 production panel files
2019-12-12 corrected panel to 1x5
    previsously it was 1x6, so we wanted to keep it the same as before and good for pnp machines.
2019-12-12 renaming zip file to ensure correct file gets used for ordering.
2019-12-13 removed old/bad production files and update readme
2019-12-13 Update to correct file name
    no changes to design, just file name
2019-12-13 controller bit text logo update
2019-12-13 Control:bit logo to Controller:bit
    Also bumped version to v21 in brd and sch, to ensure correct panel files are used.
2019-12-13 Production panel v21 (array 1x5)
2019-12-16 Schematic cleanup
    -removed pesky test point values (overlap)
2020-03-20 Update README.md
    adjust naming
2020-07-14 Update Examples for Gamer:Bit Extension v0.0.8
    MakeCode Editor updated recently which caused the code to break due to a bug was initially ignored by the editor. There was a patch to the bug in the gamer:bit extension which was updated to v0.0.8 s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
    The names of the following examples were also adjusted for consistency.

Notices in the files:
parts and their libraries:
SparkFun-Aesthetics: Licensing: Creative Commons ShareAlike 4.0 International - https://creativecommons.org/licenses/by-sa/4.0
SparkFun-Aesthetics: Released under the Creative Commons Attribution Share-Alike 4.0 License
SparkFun-Aesthetics: https://creativecommons.org/licenses/by-sa/4.0
